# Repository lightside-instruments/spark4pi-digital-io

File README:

spark4pi-* is a modular hardware platform for managed
instrument implementations controlled over Raspberry Pi
compatible 40 pin interface. The design is inspired by 
the Spark hardware platform for networking as form factor
but with a Raspberry Pi 40 pin connector as management
interface instead of 96boards.

The spark4pi-digital-io
has 6x SMA connectors connected to input (3.3V or 1.65V)
and output drivers (3.3V or 5V with open-circuit and 1.65V
or 2.5V with 50 ohm termination )
with configurable direction that are connected to GPIOs on the
Raspberry Pi connector. 2 GPIOs per channel one for selection of
direction and one for the actual signal.

The project includes the following components:
1. board - schematic and PCB design files for KiCAD
2. mechanical - technical documentation for production
 of a 1U 19 inch rack mountable ESD Acrylic box.
3. board-pi-bridge - design files for board that
 connects together a Pi compatible board with the instrument
 extension base board mounted to the left of the Pi compatible
 control board.

The project is published by Lightside Instruments AS
under TAPR Open Hardware License. Read the LICENSE file
for details.

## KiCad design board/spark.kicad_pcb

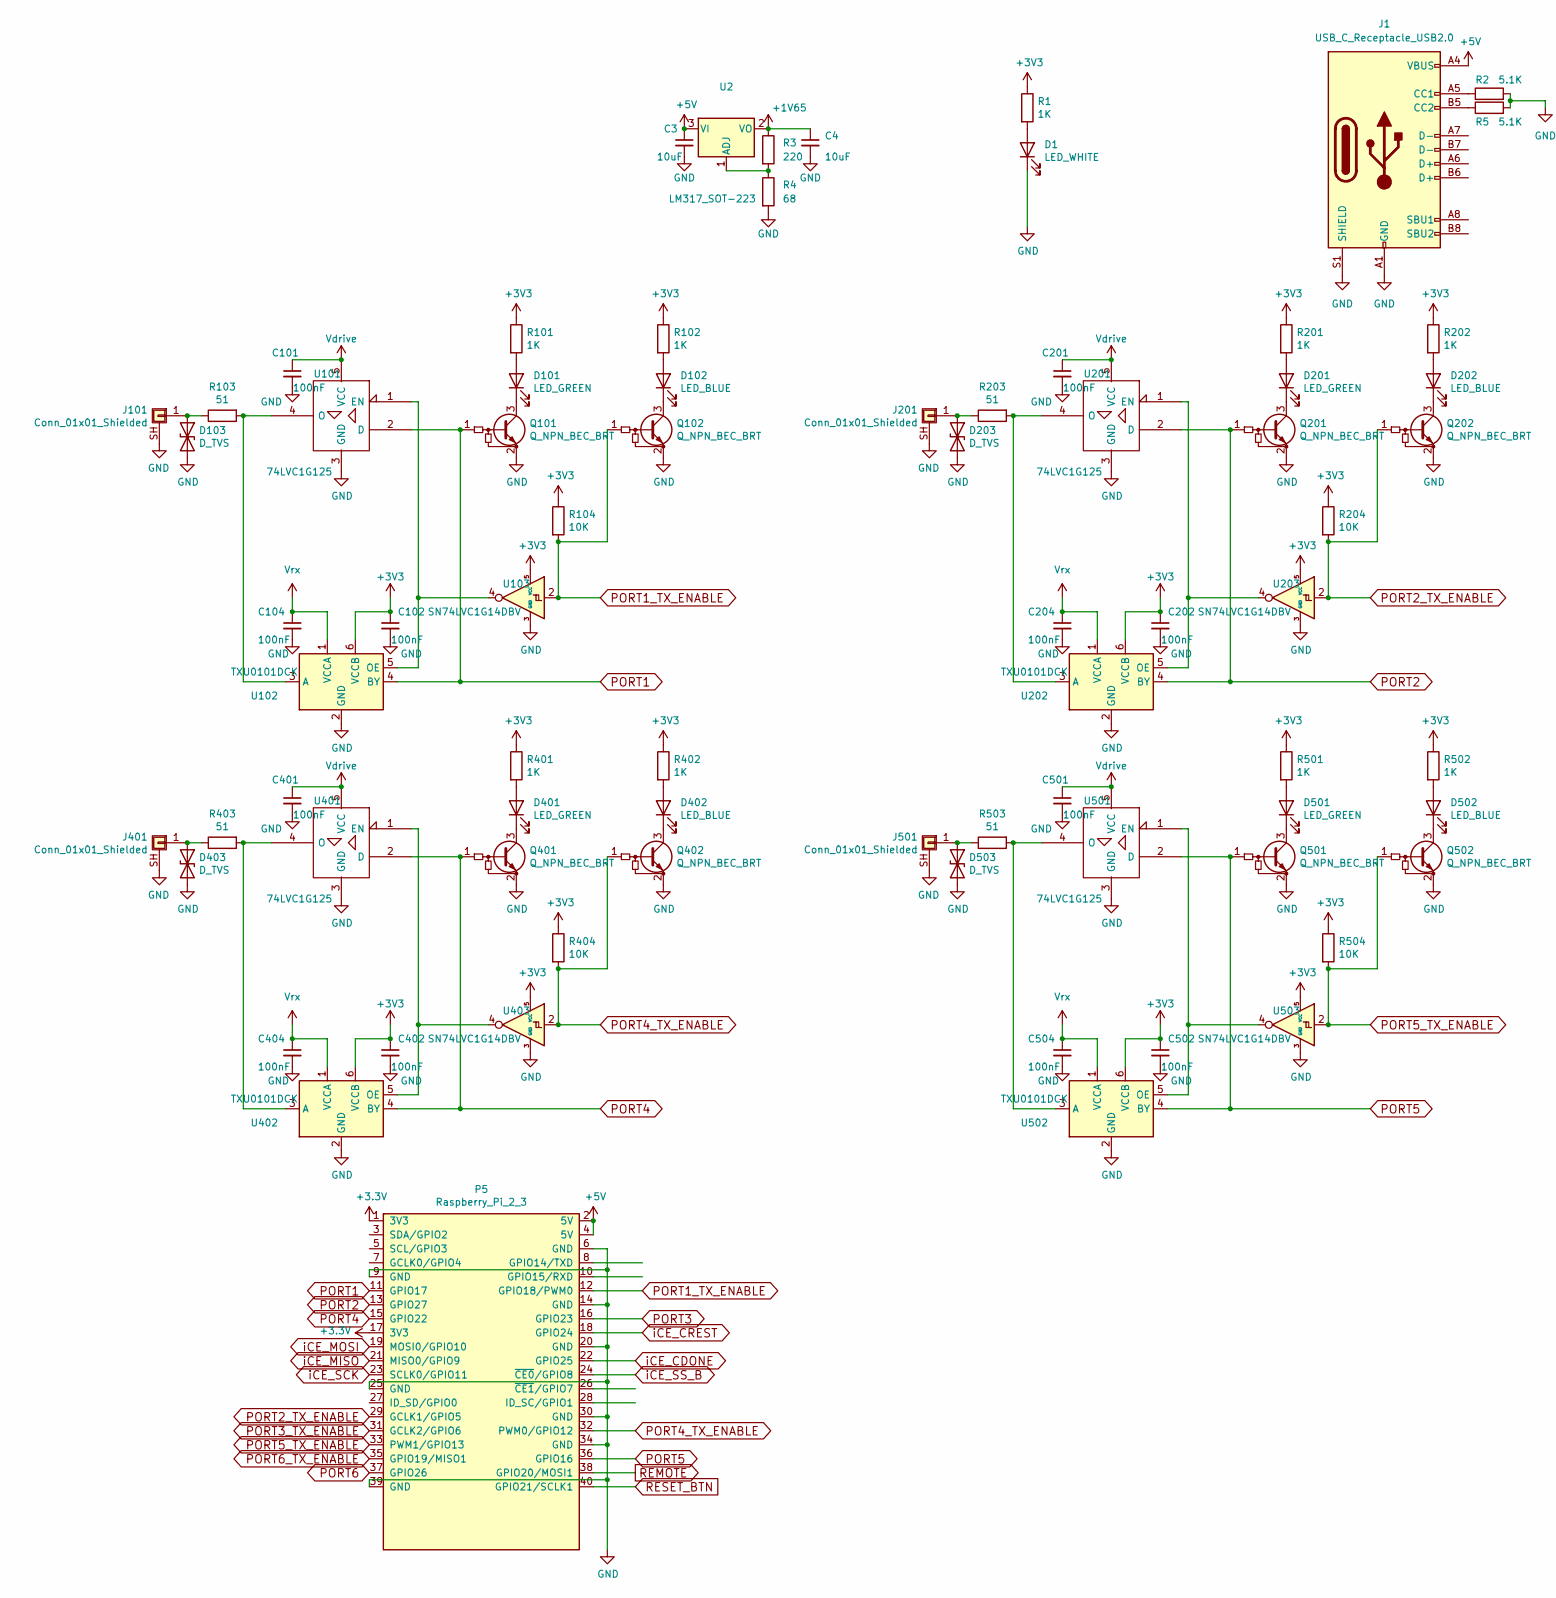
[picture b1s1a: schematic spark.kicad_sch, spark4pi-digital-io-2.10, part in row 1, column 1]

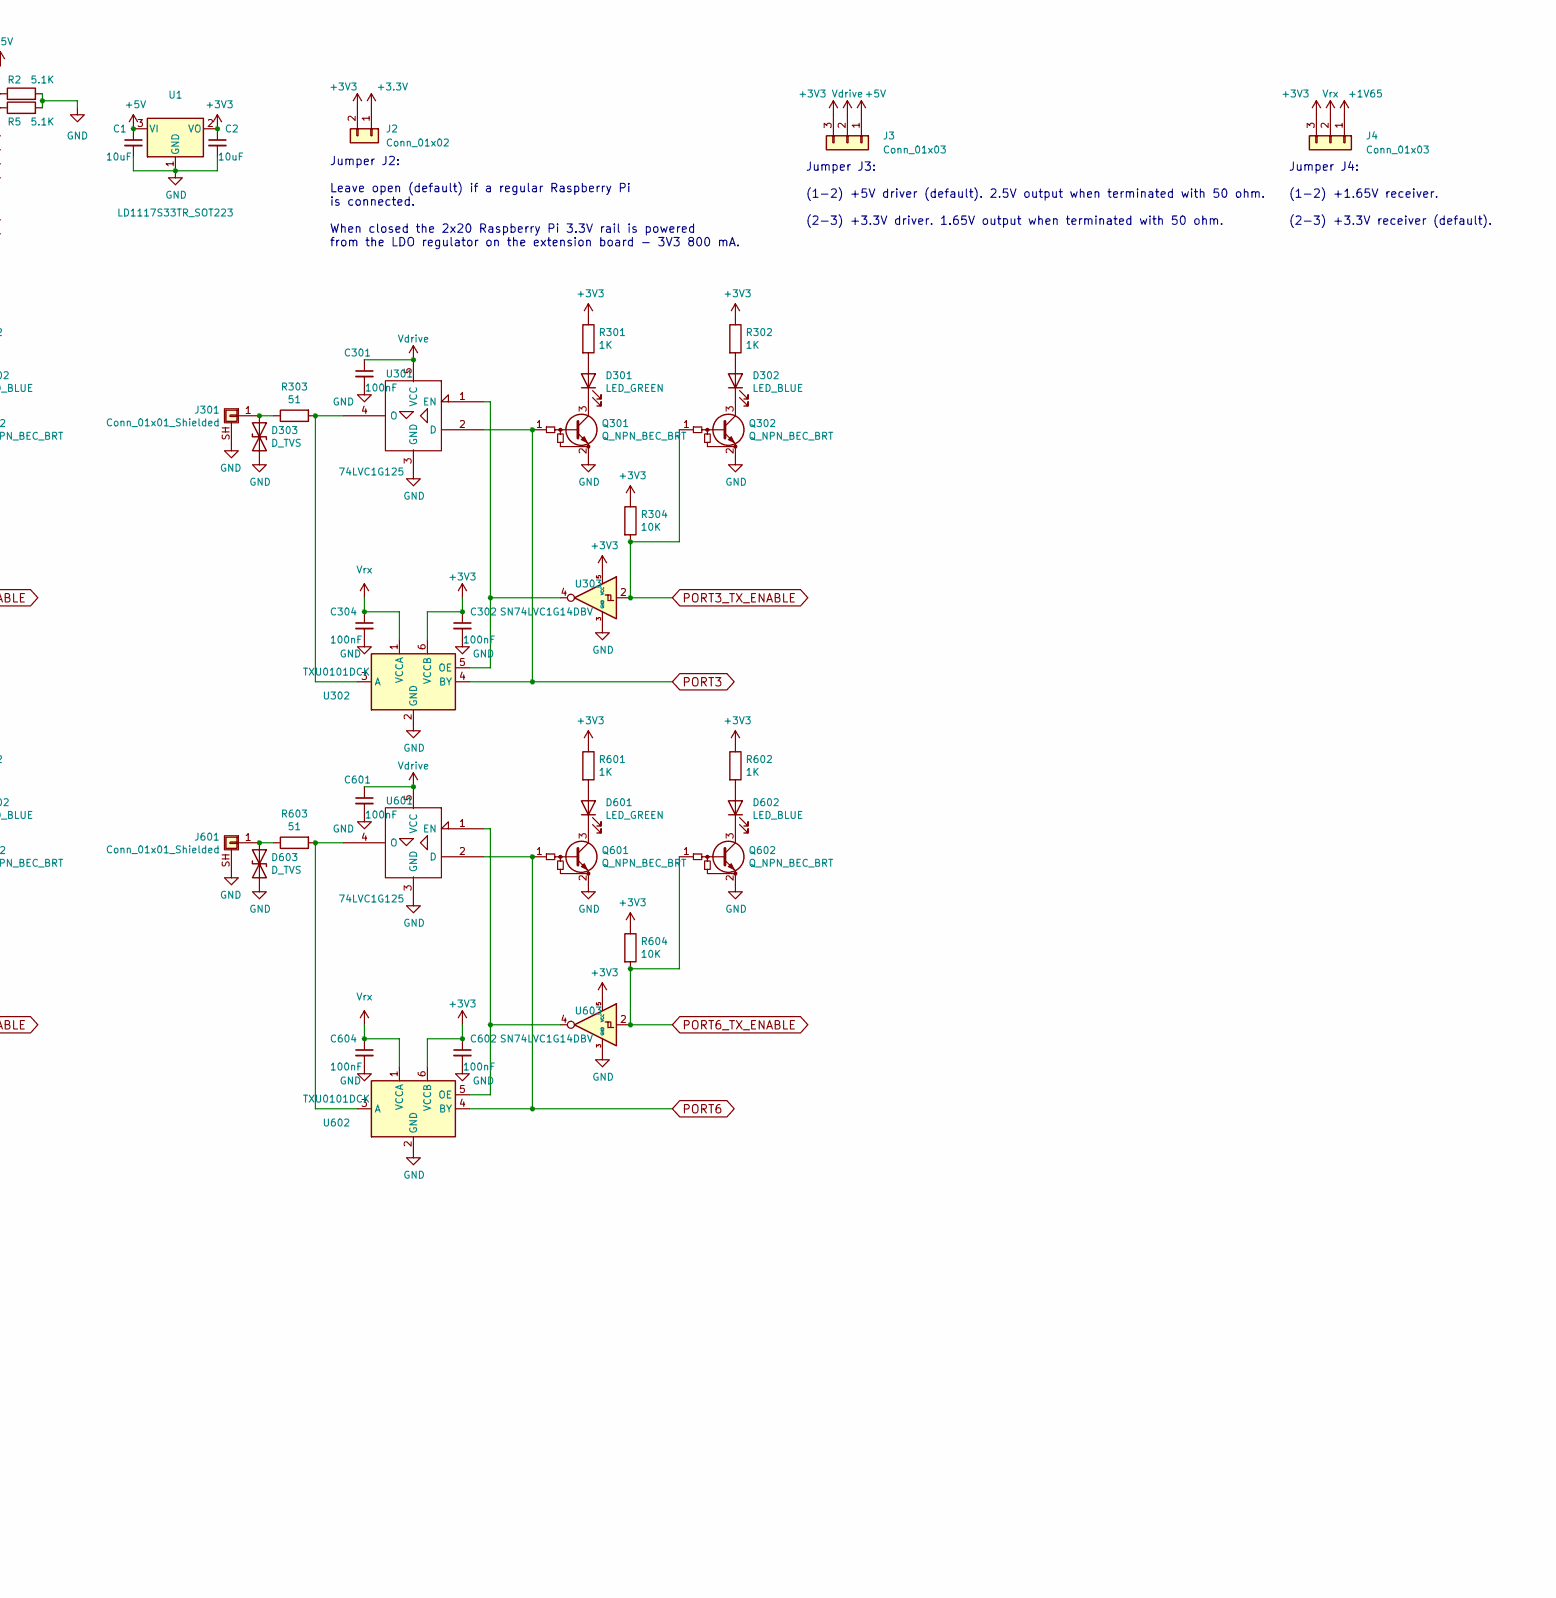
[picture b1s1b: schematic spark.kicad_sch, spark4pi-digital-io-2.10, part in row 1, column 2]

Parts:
C1, C2, C3, C4: 10uF; C_0402_1005Metric
C101, C102, C104, C201, C202, C204, C301, C302, C304, C401, C402, C404, C501, C502, C504, C601, C602, C604: 100nF; C_0402_1005Metric
D1: LED_WHITE; LED_0603_1608Metric
D101, D201, D301, D401, D501, D601: LED_GREEN; LED_0603_1608Metric
D102, D202, D302, D402, D502, D602: LED_BLUE; LED_0603_1608Metric
D103, D203, D303, D403, D503, D603: D_TVS; R_0402_1005Metric
J1: USB_C_Receptacle_USB2.0; USB_C_Receptacle_GCT_USB4105-xx-A_16P_TopMnt_Horizontal
J2: Conn_01x02; PinHeader_2x01_P2.54mm_Vertical
J3, J4: Conn_01x03; PinHeader_1x03_P2.54mm_Vertical
J101, J201, J301, J401, J501, J601: Conn_01x01_Shielded; SMA_LINX_CONSMA002_Horizontal
P5: Raspberry_Pi_2_3; PinHeader_2x20_P2.54mm_Vertical_1_04mm
Q101, Q102, Q201, Q202, Q301, Q302, Q401, Q402, Q501, Q502, Q601, Q602: Q_NPN_BEC_BRT; SOT-323_SC-70
R1, R101, R102, R201, R202, R301, R302, R401, R402, R501, R502, R601, R602: 1K; R_0402_1005Metric
R2, R5: 5.1K; R_0402_1005Metric
R3: 220; R_0402_1005Metric
R4: 68; R_0402_1005Metric
R103, R203, R303, R403, R503, R603: 51; R_0805_2012Metric
R104, R204, R304, R404, R504, R604: 10K; R_0402_1005Metric
U1: LD1117S33TR_SOT223; SOT-223-3_TabPin2
U2: LM317_SOT-223; SOT-223-3_TabPin2
U101, U201, U301, U401, U501, U601: 74LVC1G125; TSOP-5_1.65x3.05mm_P0.95mm
U102, U202, U302, U402, U502, U602: TXU0101DCK; SOT-363_SC-70-6
U103, U203, U303, U403, U503, U603: SN74LVC1G14DBV; SOT-23-5

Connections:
+1V65: C4.1, J4.1, R3.1, U2.2 (VO)
+3.3V: J2.1, P5.1 (3V3), P5.17 (3V3)
+3V3: C2.1, C102.1, C202.1, C302.1, C402.1, C502.1, C602.1, J2.2, J3.3, J4.3, R1.1, R101.1, R102.1, R104.1, R201.1, R202.1, R204.1, R301.1, R302.1, R304.1, R401.1, R402.1, R404.1, R501.1, R502.1, R504.1, R601.1, R602.1, R604.1, U1.2 (VO), U102.6 (VCCB), U103.5 (VCC), U202.6 (VCCB), U203.5 (VCC), U302.6 (VCCB), U303.5 (VCC), U402.6 (VCCB), U403.5 (VCC), U502.6 (VCCB), U503.5 (VCC), U602.6 (VCCB), U603.5 (VCC)
+5V: C1.1, C3.1, J1.A4 (VBUS), J1.A9 (VBUS), J1.B4 (VBUS), J1.B9 (VBUS), J3.1, P5.2 (5V), P5.4 (5V), U1.3 (VI), U2.3 (VI)
GND: C1.2, C2.2, C3.2, C4.2, C101.2, C102.2, C104.2, C201.2, C202.2, C204.2, C301.2, C302.2, C304.2, C401.2, C402.2, C404.2, C501.2, C502.2, C504.2, C601.2, C602.2, C604.2, D1.1 (K), D103.2 (A2), D203.2 (A2), D303.2 (A2), D403.2 (A2), D503.2 (A2), D603.2 (A2), J1.A1 (GND), J1.A12 (GND), J1.B1 (GND), J1.B12 (GND), J1.S1 (SHIELD), J101.SH (Shield), J201.SH (Shield), J301.SH (Shield), J401.SH (Shield), J501.SH (Shield), J601.SH (Shield), P5.6 (GND), P5.9 (GND), P5.14 (GND), P5.20 (GND), P5.25 (GND), P5.30 (GND), P5.34 (GND), P5.39 (GND), Q101.2 (E), Q102.2 (E), Q201.2 (E), Q202.2 (E), Q301.2 (E), Q302.2 (E), Q401.2 (E), Q402.2 (E), Q501.2 (E), Q502.2 (E), Q601.2 (E), Q602.2 (E), R2.2, R4.2, R5.2, U1.1 (GND), U101.3 (GND), U102.2 (GND), U103.3 (GND), U201.3 (GND), U202.2 (GND), U203.3 (GND), U301.3 (GND), U302.2 (GND), U303.3 (GND), U401.3 (GND), U402.2 (GND), U403.3 (GND), U501.3 (GND), U502.2 (GND), U503.3 (GND), U601.3 (GND), U602.2 (GND), U603.3 (GND)
unnamed: D1.2 (A), R1.2
unnamed: D101.1 (K), Q101.3 (C)
unnamed: D101.2 (A), R101.2
unnamed: D102.1 (K), Q102.3 (C)
unnamed: D102.2 (A), R102.2
unnamed: D103.1 (A1), J101.1, R103.1
unnamed: D201.1 (K), Q201.3 (C)
unnamed: D201.2 (A), R201.2
unnamed: D202.1 (K), Q202.3 (C)
unnamed: D202.2 (A), R202.2
unnamed: D203.1 (A1), J201.1, R203.1
unnamed: D301.1 (K), Q301.3 (C)
unnamed: D301.2 (A), R301.2
unnamed: D302.1 (K), Q302.3 (C)
unnamed: D302.2 (A), R302.2
unnamed: D303.1 (A1), J301.1, R303.1
unnamed: D401.1 (K), Q401.3 (C)
unnamed: D401.2 (A), R401.2
unnamed: D402.1 (K), Q402.3 (C)
unnamed: D402.2 (A), R402.2
unnamed: D403.1 (A1), J401.1, R403.1
unnamed: D501.1 (K), Q501.3 (C)
unnamed: D501.2 (A), R501.2
unnamed: D502.1 (K), Q502.3 (C)
unnamed: D502.2 (A), R502.2
unnamed: D503.1 (A1), J501.1, R503.1
unnamed: D601.1 (K), Q601.3 (C)
unnamed: D601.2 (A), R601.2
unnamed: D602.1 (K), Q602.3 (C)
unnamed: D602.2 (A), R602.2
unnamed: D603.1 (A1), J601.1, R603.1
unnamed: J1.A5 (CC1), R2.1
unnamed: J1.B5 (CC2), R5.1
unnamed: R3.2, R4.1, U2.1 (ADJ)
unnamed: R103.2, U101.4 (O), U102.3 (A)
unnamed: R203.2, U201.4 (O), U202.3 (A)
unnamed: R303.2, U301.4 (O), U302.3 (A)
unnamed: R403.2, U401.4 (O), U402.3 (A)
unnamed: R503.2, U501.4 (O), U502.3 (A)
unnamed: R603.2, U601.4 (O), U602.3 (A)
unnamed: U101.1 (EN), U102.5 (OE), U103.4
unnamed: U201.1 (EN), U202.5 (OE), U203.4
unnamed: U301.1 (EN), U302.5 (OE), U303.4
unnamed: U401.1 (EN), U402.5 (OE), U403.4
unnamed: U501.1 (EN), U502.5 (OE), U503.4
unnamed: U601.1 (EN), U602.5 (OE), U603.4
PORT1: P5.11 (GPIO17), Q101.1 (B), U101.2 (D), U102.4 (BY)
PORT1_TX_ENABLE: P5.12 (GPIO18/PWM0), Q102.1 (B), R104.2, U103.2
PORT2: P5.13 (GPIO27), Q201.1 (B), U201.2 (D), U202.4 (BY)
PORT2_TX_ENABLE: P5.29 (GCLK1/GPIO5), Q202.1 (B), R204.2, U203.2
PORT3: P5.16 (GPIO23), Q301.1 (B), U301.2 (D), U302.4 (BY)
PORT3_TX_ENABLE: P5.31 (GCLK2/GPIO6), Q302.1 (B), R304.2, U303.2
PORT4: P5.15 (GPIO22), Q401.1 (B), U401.2 (D), U402.4 (BY)
PORT4_TX_ENABLE: P5.32 (PWM0/GPIO12), Q402.1 (B), R404.2, U403.2
PORT5: P5.36 (GPIO16), Q501.1 (B), U501.2 (D), U502.4 (BY)
PORT5_TX_ENABLE: P5.33 (PWM1/GPIO13), Q502.1 (B), R504.2, U503.2
PORT6: P5.37 (GPIO26), Q601.1 (B), U601.2 (D), U602.4 (BY)
PORT6_TX_ENABLE: P5.35 (GPIO19/MISO1), Q602.1 (B), R604.2, U603.2
REMOTE: P5.38 (GPIO20/MOSI1)
RESET_BTN: P5.40 (GPIO21/SCLK1)
Vdrive: C101.1, C201.1, C301.1, C401.1, C501.1, C601.1, J3.2, U101.5 (VCC), U201.5 (VCC), U301.5 (VCC), U401.5 (VCC), U501.5 (VCC), U601.5 (VCC)
Vrx: C104.1, C204.1, C304.1, C404.1, C504.1, C604.1, J4.2, U102.1 (VCCA), U202.1 (VCCA), U302.1 (VCCA), U402.1 (VCCA), U502.1 (VCCA), U602.1 (VCCA)
iCE_CDONE: P5.22 (GPIO25)
iCE_CREST: P5.18 (GPIO24)
iCE_MISO: P5.21 (MISO0/GPIO9)
iCE_MOSI: P5.19 (MOSI0/GPIO10)
iCE_SCK: P5.23 (SCLK0/GPIO11)
iCE_SS_B: P5.24 (~CE0/GPIO8)

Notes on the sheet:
Jumper J3: (1-2) +5V driver (default). 2.5V output when terminated with 50 ohm. (2-3) +3.3V driver. 1.65V output when terminated with 50 ohm.
Jumper J4: (1-2) +1.65V receiver. (2-3) +3.3V receiver (default).
Jumper J2: Leave open (default) if a regular Raspberry Pi is connected. When closed the 2x20 Raspberry Pi 3.3V rail is powered from the LDO regulator on the extension board - 3V3 800 mA.

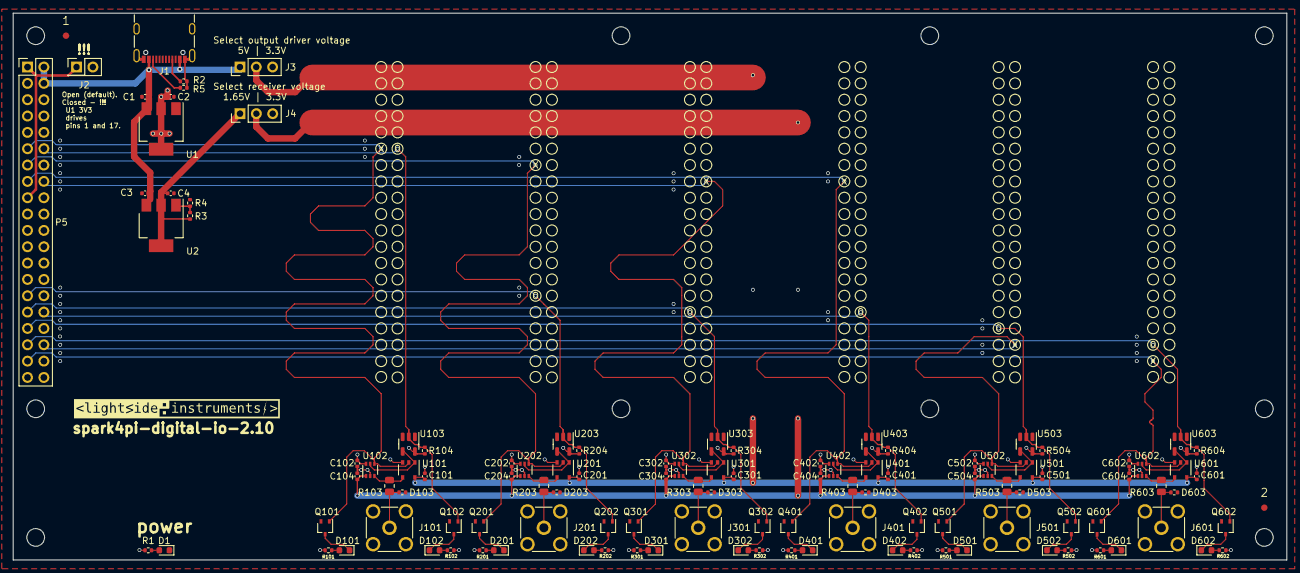
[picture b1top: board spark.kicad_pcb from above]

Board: 4 copper layers, 198.0 x 85.0 mm, 121 parts (0 on the bottom side), 65 nets.

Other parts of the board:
1, 2: (no value)
Ref**: Val**; raspberry-pi-signal-interface-silks
Ref**#2, Ref**#3, Ref**#4, Ref**#5, Ref**#6: Val**; raspberry-pi-signal-interface-silks

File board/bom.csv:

Reference,Quantity,footprint,Value,Tolerance,Voltage,Current,Power,Mfr Part #
"J101,J201,J301,J401,J601,J501",6,SMA_LINX_CONSMA002_Horizontal,Conn_01x01_Shielded,,,,,CONSMA002-L
R2,1,R_0402_1005Metric,5.1K,,,,,ERJ-2RKF5101X
"U601,U101,U301,U402,U102,U501,U602,U302,U401,U502,U201,U202",12,TSOP-5_1.65x3.05mm_P0.95mm,74LVC1G125,,,,,"74LVC1G125GV,125"
"D301,D101,D601,D501,D201,D401",6,LED_0603_1608Metric,LED_GREEN,,,,,"
150040VS73240"
"Q602,Q202,Q601,Q102,Q101,Q501,Q502,Q401,Q302,Q301,Q201,Q402",12,SOT-323_SC-70,Q_NPN_BEC_BRT,,,,,"PDTC114EU,115"
"U403,U103,U203,U303,U603,U503",6,SOT-23-5,SN74LVC1G14DBV,,,,,SN74LVC1G14DBV
"C401,C402,C302,C301,C101,C602,C502,C201,C601,C102,C202,C501",12,C_0402_1005Metric,100nF,,,,,885012205037
"D102,D302,D202,D502,D402,D602",6,LED_0603_1608Metric,LED_BLUE,,,,,"
150040VS73240"
"R504,R604,R304,R204,R404,R104",6,R_0402_1005Metric,10K,,,,,CRCW040210K0FKEDC
"D103,D603,D403,D503,D303,D203",6,R_0402_1005Metric,D_TVS,,,,,PESD0402-140
"C2,C1",2,C_0402_1005Metric,10uF,,,,,ZRB15XR61A106ME01D
"R203,R403,R603,R503,R303,R103",6,R_0805_2012Metric,51,,,,,ERJ-P06J510V
D1,1,LED_0603_1608Metric,LED_WHITE,,,,,150060VS55040
"R301,R401,R1,R502,R302,R101,R402,R602,R601,R501,R202,R201,R102",13,R_0402_1005Metric,1K,,,,,ERJ-2GEJ102X
P5,1,PinHeader_2x20_P2.54mm_Vertical_1_04mm,Raspberry_Pi_2_3,,,,,SSW-120-01-T-D-006
J3,1,PinHeader_1x03_P2.54mm_Vertical,Conn_01x03,,,,,M20-9770346
J2,1,PinHeader_2x01_P2.54mm_Vertical,Conn_01x02,,,,,M20-9990246
U1,1,SOT-223-3_TabPin2,LD1117S33TR_SOT223,,,,,LD1117S33TR 
J1,1,USB_C_Receptacle_GCT_USB4105-xx-A_16P_TopMnt_Horizontal,USB_C_Receptacle_USB2.0,,,,,USB4105-GF-A

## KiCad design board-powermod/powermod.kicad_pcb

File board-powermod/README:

powermod-tps54202 is a simple DC-DC regulator board
developed by Lightside Instruments AS.

The project includes schematic and PCB
design files for KiCAD.

The project is published by Lightside Instruments AS
under TAPR Open Hardware License. Read the LICENSE file
for details.

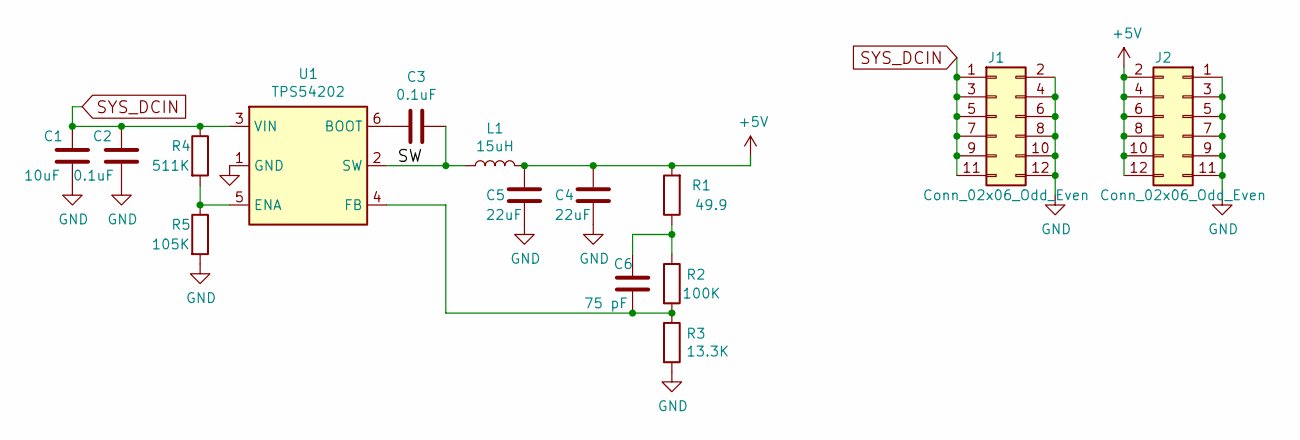
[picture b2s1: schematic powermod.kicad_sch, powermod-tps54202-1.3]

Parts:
C1: 10uF; C_0603_1608Metric
C2, C3: 0.1uF; C_0402_1005Metric
C4, C5: 22uF; C_0805_2012Metric
C6: 75 pF; C_0402_1005Metric
J1, J2: Conn_02x06_Odd_Even; PinHeader_2x06_P2.00mm_Vertical_SMD
L1: 15uH; L_Taiyo-Yuden_MD-5050
R1: 49.9; R_0402_1005Metric
R2: 100K; R_0402_1005Metric
R3: 13.3K; R_0402_1005Metric
R4: 511K; R_0402_1005Metric
R5: 105K; R_0402_1005Metric
U1: TPS54202; SOT-23-6

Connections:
+5V: C4.1, C5.1, J2.2, J2.4, J2.6, J2.8, J2.10, J2.12, L1.2, R1.2
/SW: C3.1, L1.1, U1.2 (SW)
GND: C1.2, C2.2, C4.2, C5.2, J1.2, J1.4, J1.6, J1.8, J1.10, J1.12, J2.1, J2.3, J2.5, J2.7, J2.9, J2.11, R3.2, R5.2, U1.1 (GND)
unnamed: C3.2, U1.6 (BOOT)
unnamed: C6.1, R1.1, R2.1
unnamed: C6.2, R2.2, R3.1, U1.4 (FB)
unnamed: R4.2, R5.1, U1.5 (ENA)
SYS_DCIN: C1.1, C2.1, J1.1, J1.3, J1.5, J1.7, J1.9, J1.11, R4.1, U1.3 (VIN)

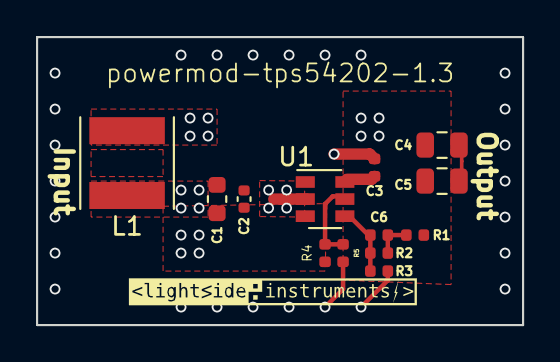
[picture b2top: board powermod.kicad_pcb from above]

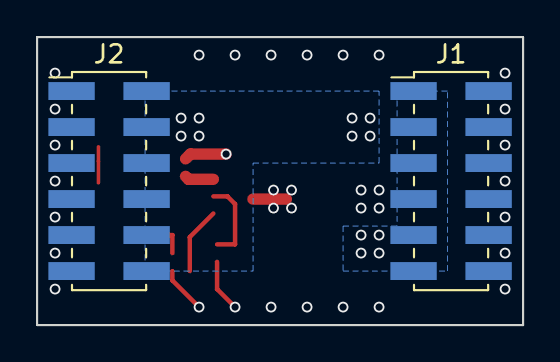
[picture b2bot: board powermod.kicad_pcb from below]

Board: 4 copper layers, 27.0 x 16.0 mm, 16 parts (2 on the bottom side), 8 nets.

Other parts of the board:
svg2mod: G***; lsi-logo-16mm

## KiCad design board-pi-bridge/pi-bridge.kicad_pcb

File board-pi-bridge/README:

pi-bridge is an open hardware adapter board for connecting
Raspberry Pi to base board mounted at the same level
to the right side of the Pi board.

The initial release pi-bridge includes schematic and PCB
design files for KiCAD.

The project is published by Lightside Instruments AS
under TAPR Open Hardware License. Read the LICENSE file
for details.

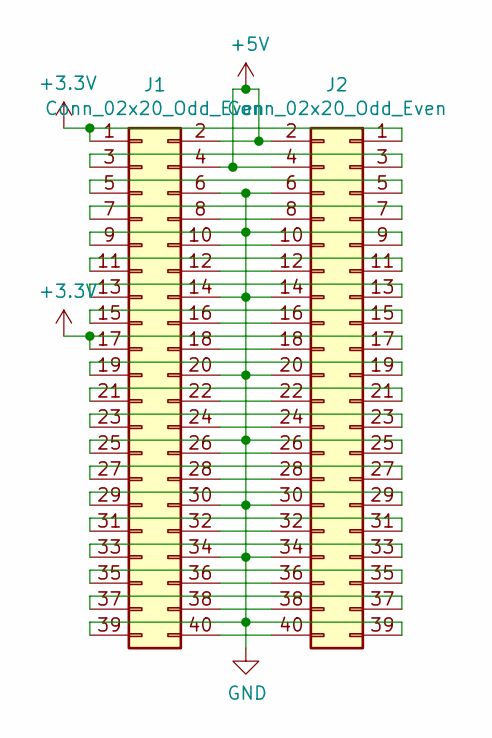
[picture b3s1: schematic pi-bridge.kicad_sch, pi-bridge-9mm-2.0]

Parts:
J1, J2: Conn_02x20_Odd_Even; PinSocket_2x20_P2.54mm_Vertical_1_04mm

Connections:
+3.3V: J1.1, J1.17, J2.1, J2.17
+5V: J1.2, J1.4, J2.2, J2.4
GND: J1.6, J1.9, J1.14, J1.20, J1.25, J1.30, J1.34, J1.39, J2.6, J2.9, J2.14, J2.20, J2.25, J2.30, J2.34, J2.39
unnamed: J1.3, J2.3
unnamed: J1.5, J2.5
unnamed: J1.7, J2.7
unnamed: J1.8, J2.8
unnamed: J1.10, J2.10
unnamed: J1.11, J2.11
unnamed: J1.12, J2.12
unnamed: J1.13, J2.13
unnamed: J1.15, J2.15
unnamed: J1.16, J2.16
unnamed: J1.18, J2.18
unnamed: J1.19, J2.19
unnamed: J1.21, J2.21
unnamed: J1.22, J2.22
unnamed: J1.23, J2.23
unnamed: J1.24, J2.24
unnamed: J1.26, J2.26
unnamed: J1.27, J2.27
unnamed: J1.28, J2.28
unnamed: J1.29, J2.29
unnamed: J1.31, J2.31
unnamed: J1.32, J2.32
unnamed: J1.33, J2.33
unnamed: J1.35, J2.35
unnamed: J1.36, J2.36
unnamed: J1.37, J2.37
unnamed: J1.38, J2.38
unnamed: J1.40, J2.40

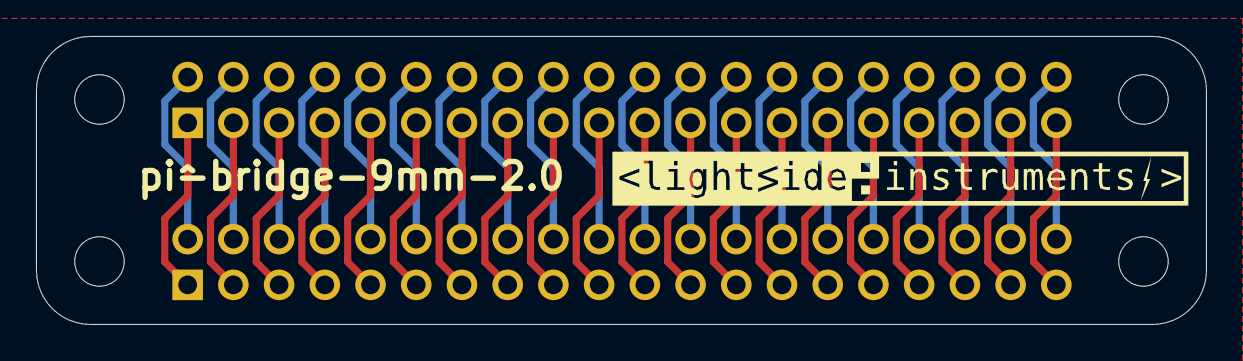
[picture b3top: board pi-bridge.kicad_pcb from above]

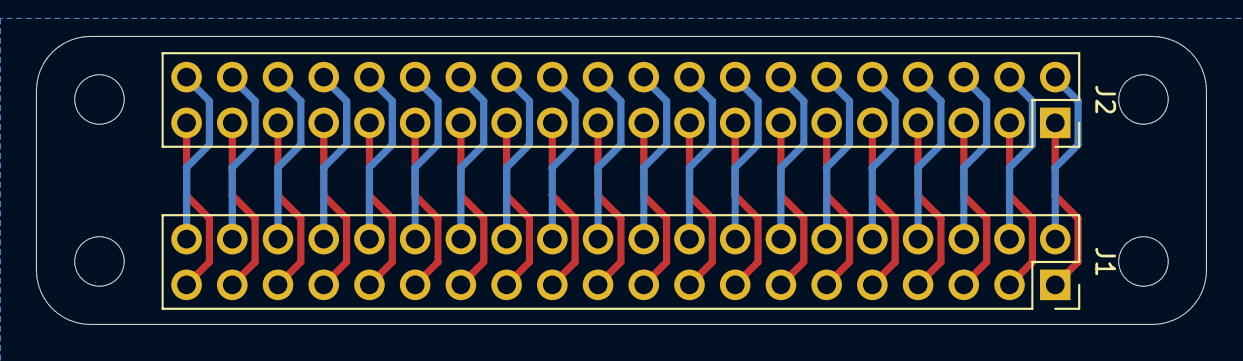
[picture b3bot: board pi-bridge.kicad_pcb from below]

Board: 4 copper layers, 65.0 x 16.0 mm, 3 parts (2 on the bottom side), 31 nets.

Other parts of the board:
svg2mod: G***; lsi-logo-32mm

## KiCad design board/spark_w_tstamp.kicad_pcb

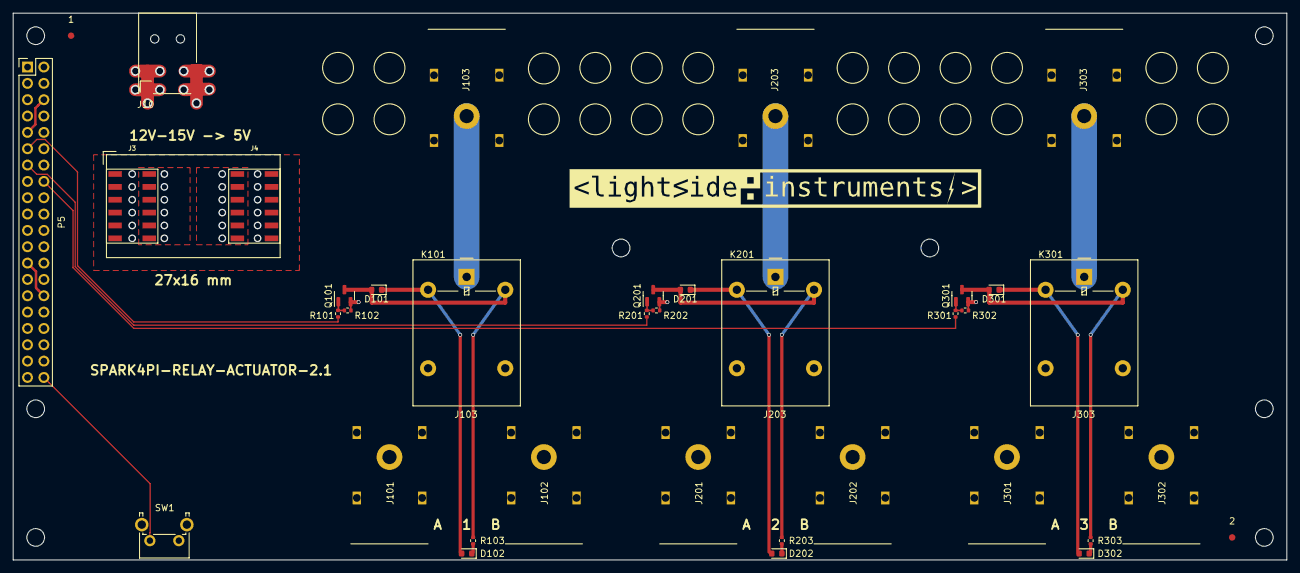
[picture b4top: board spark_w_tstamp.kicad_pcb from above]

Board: 4 copper layers, 198.0 x 85.0 mm, 37 parts (0 on the bottom side), 26 nets.

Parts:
1, 2: Fiducial_1mm_Mask3mm
D101, D201, D301: D_Schottky; D_0603_1608Metric
D102, D202, D302: LED; D_0603_1608Metric
J3, J4: Conn_02x06_Odd_Even; Socket_Strip_SMD_2x6_Pitch2mm
J10: Barrel_Jack; PJ1-021-SMT-TR
J101, J102, J103, J201, J202, J203, J301, J302, J303: Conn_01x01; banana-plug-horizontal-black
K101, K201, K301: G5LE-1; Relay_SPDT_Omron-G5LE-1
P5: Raspberry_Pi_2_3; PinHeader_2x20_P2.54mm_Vertical_1_04mm
Q101, Q201, Q301: BS870; SOT-23
R101, R201, R301: 10K; R_0402_1005Metric
R102, R103, R202, R203, R302, R303: 1K; R_0402_1005Metric
SW1: SW_Push; SW_Tactile_SPST_Angled_PTS645Vx83-2LFS

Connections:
+3.3V: P5.1 (3V3), P5.17 (3V3)
+5V: J4.1, J4.3, J4.5, J4.7, J4.9, J4.11, P5.2 (5V), P5.4 (5V)
GND: J3.1, J3.3, J3.5, J3.7, J3.9, J3.11, J4.2, J4.4, J4.6, J4.8, J4.10, J4.12, J10.2, J10.3, P5.6 (GND), P5.9 (GND), P5.14 (GND), P5.20 (GND), P5.25 (GND), P5.30 (GND), P5.34 (GND), P5.39 (GND), Q101.2 (S), Q201.2 (S), Q301.2 (S), R101.2, R201.2, R301.2, SW1.1
IN1: J103.1, K101.1
IN2: J203.1, K201.1
IN3: J303.1, K301.1
unnamed: D101.2 (A), K101.5, Q101.3 (D), R103.2
unnamed: D102.1 (K), R103.1
unnamed: D201.2 (A), K201.5, Q201.3 (D), R203.2
unnamed: D202.1 (K), R203.1
unnamed: D301.2 (A), K301.5, Q301.3 (D), R303.2
unnamed: D302.1 (K), R303.1
unnamed: J101.1, K101.3
unnamed: J102.1, K101.4
unnamed: J201.1, K201.3
unnamed: J202.1, K201.4
unnamed: J301.1, K301.3
unnamed: J302.1, K301.4
unnamed: Q101.1 (G), R101.1, R102.2
unnamed: Q201.1 (G), R201.1, R202.2
unnamed: Q301.1 (G), R301.1, R302.2
PORT1: P5.11 (GPIO17), R102.1
PORT2: P5.13 (GPIO27), R202.1
PORT3: P5.16 (GPIO23), R302.1
RESET_BTN: P5.40 (GPIO21/SCLK1), SW1.2
SYS_DCIN: D101.1 (K), D102.2 (A), D201.1 (K), D202.2 (A), D301.1 (K), D302.2 (A), J3.2, J3.4, J3.6, J3.8, J3.10, J3.12, J10.1, K101.2, K201.2, K301.2

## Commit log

2023-11-28 spark-relay-actuator-pi-2-3
2023-11-28 Release spark-relay-actuator-pi-3.0
2023-11-29 Release spark-relay-actuator-pi-3.1
2023-11-29 Release spark-relay-actuator-pi-3.2
2023-12-05 Release spark-relay-actuator-pi-3.3
2023-12-27 Release spark-relay-actuator-pi-3.4
2024-01-08 Release spark4pi-relay-actuator-1.0
2024-01-09 Release spark4pi-relay-actuator-1.1
2024-01-10 Release spark4pi-relay-actuator-1.2
2024-01-11 Release spark4pi-relay-actuator-1.3
2024-01-20 Release spark4pi-relay-actuator-1.4
2024-01-24 Release spark4pi-relay-actuator-2.0
2024-02-01 Release spark4pi-relay-actuator-2.1
2024-02-02 Release spark4pi-relay-actuator-2.2
2024-02-04 Release spark4pi-relay-actuator-2.3
2024-02-07 Release spark4pi-digital-io-2.4
2024-02-08 Release spark4pi-digital-io-2.5
2024-02-09 Release spark4pi-digital-io-2.6
2024-02-09 Release spark4pi-digital-io-2.7
2024-03-16 Release spark4pi-digital-io-2.8
2024-03-18 Release spark4pi-digital-io-2.9
2024-03-31 Release spark4pi-digital-io-2.9-test1
2024-04-10 Release spark4pi-digital-io-2.10
